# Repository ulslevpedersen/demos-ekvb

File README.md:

# demos-ekvb
DEMoS Manifesto
https://arxiv.org/licenses/nonexclusive-distrib/1.0/license.html

This project contains also the tpIP implementation in F#

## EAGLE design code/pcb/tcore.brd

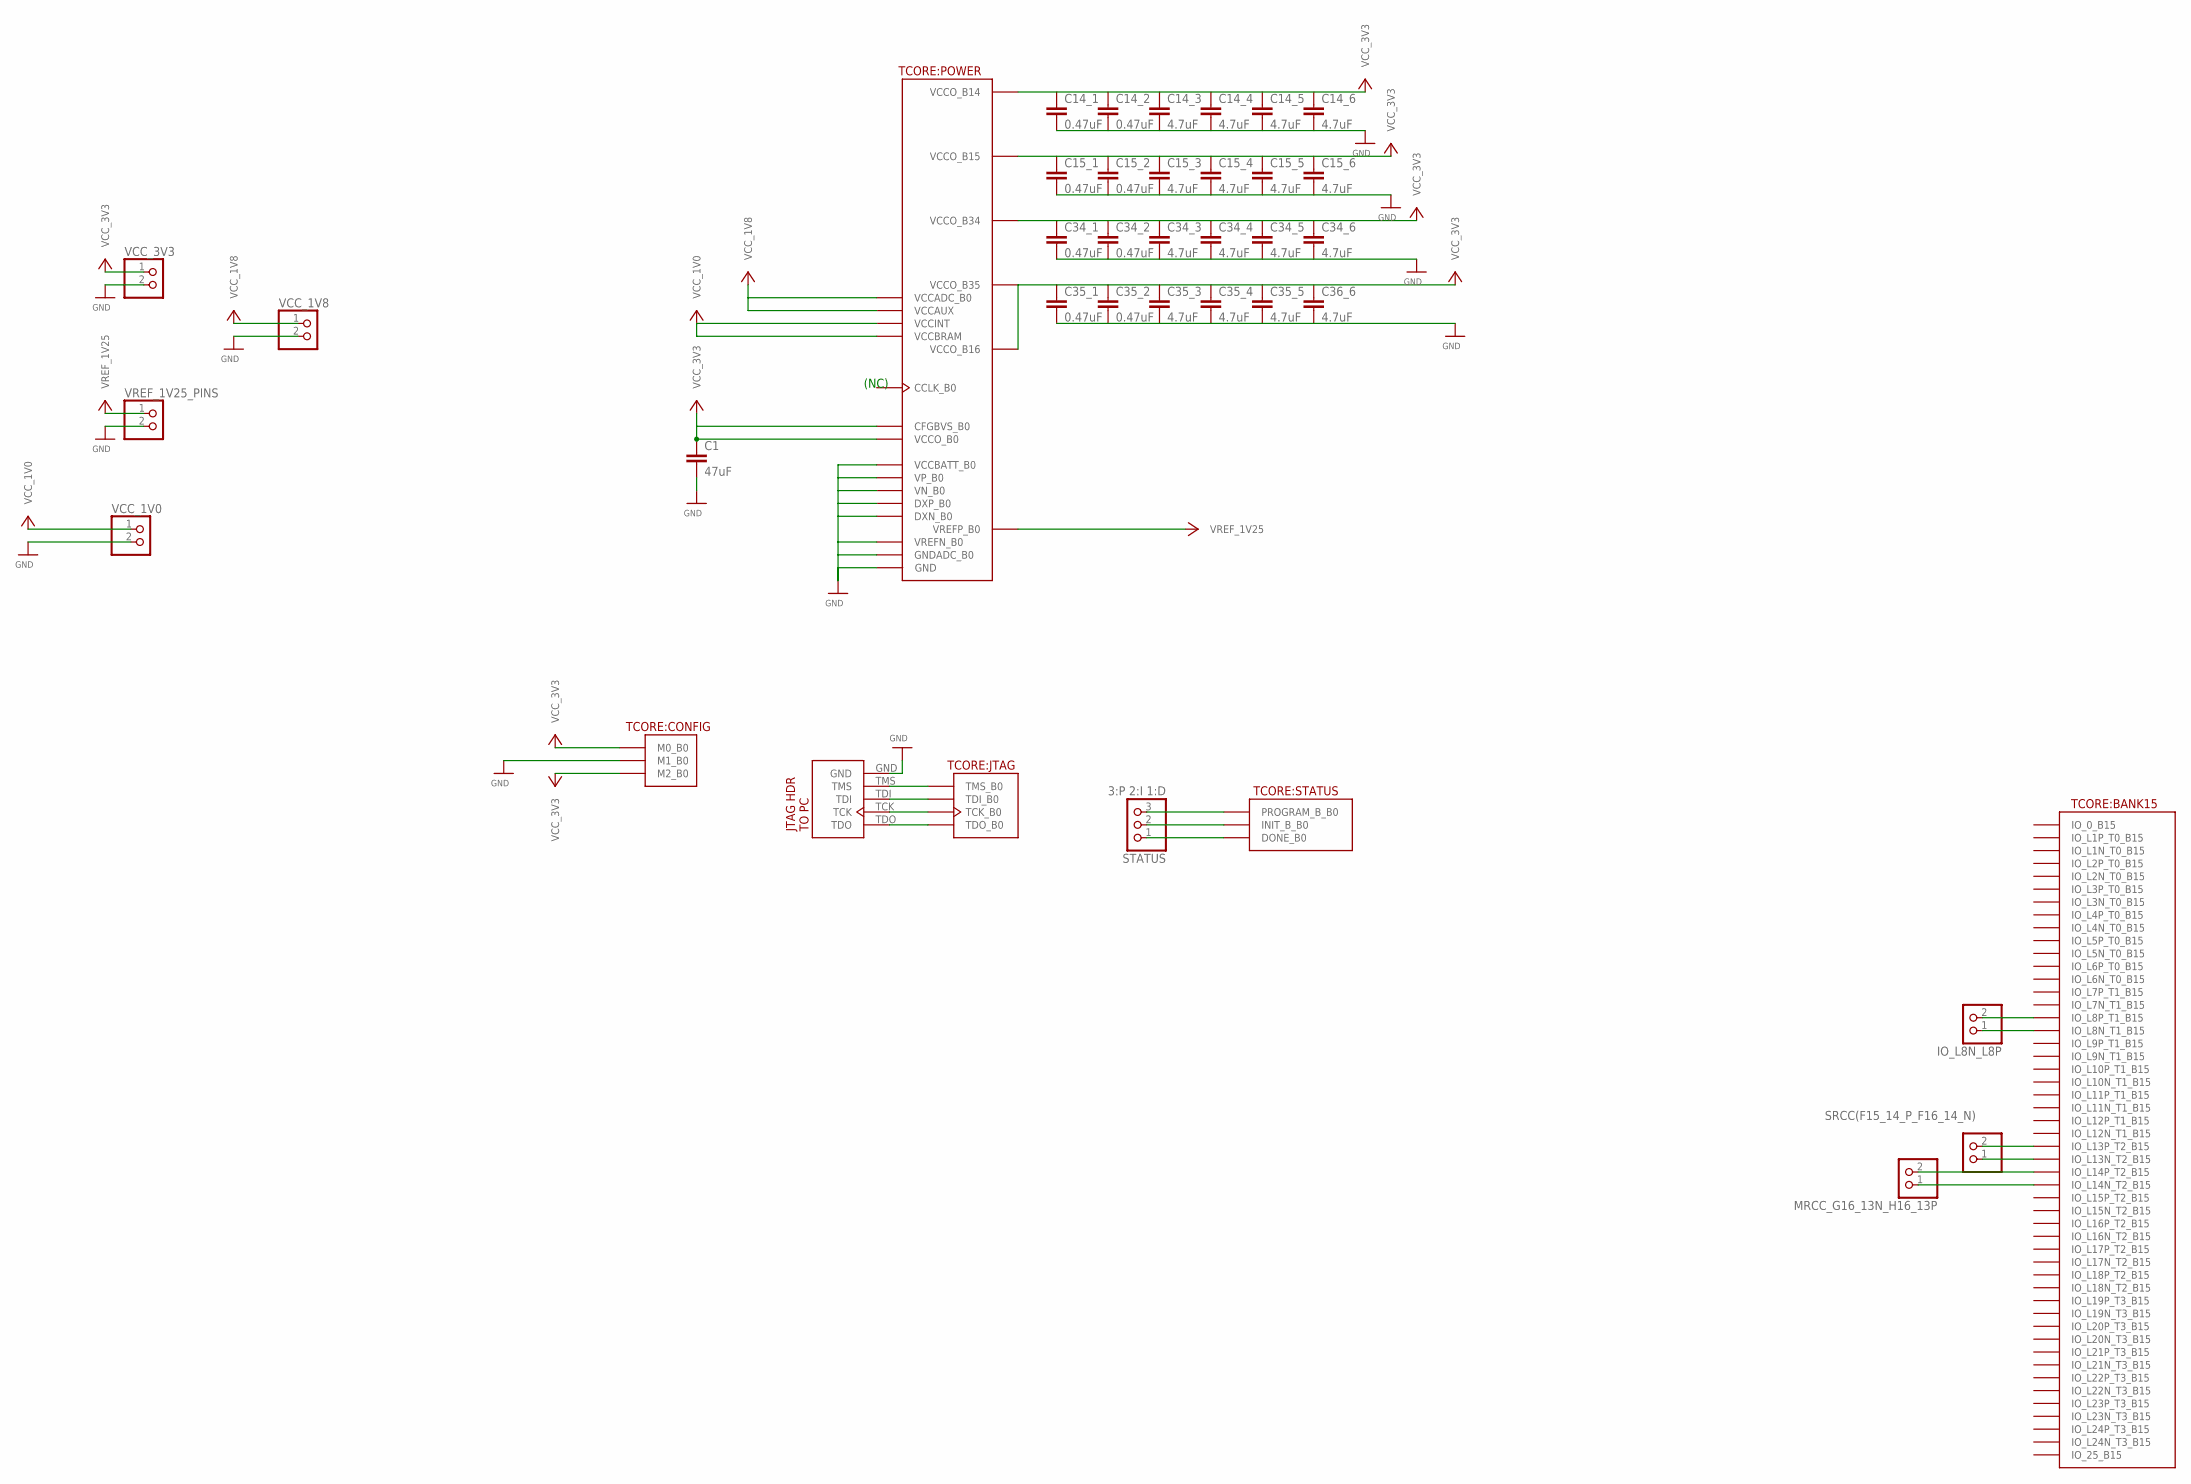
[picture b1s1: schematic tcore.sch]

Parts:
C1: 47uF; C1206
C14_1, C14_2, C15_1, C15_2, C34_1, C34_2, C35_1, C35_2: 0.47uF; C1206
C14_3, C14_4, C14_5, C14_6, C15_3, C15_4, C15_5, C15_6, C34_3, C34_4, C34_5, C34_6, C35_3, C35_4, C35_5, C36_6: 4.7uF; C1206
IO_L8N_L8P: PINHD-1X2; 1X02
JTAG_HEADER1: JTAG_HEADER; JTAG_HDR
MRCC_G16_13N_H16_13P: PINHD-1X2; 1X02
SRCC(F15_14_P_F16_14_N): PINHD-1X2; 1X02
STATUS: 3:P 2:I 1:D; 1X03
TCORE: TCORECFG324; TCORE_PAC
VCC_1V0, VCC_1V8, VCC_3V3: PINHD-1X2; 1X02
VREF_1V25_PINS: PINHD-1X2; 1X02

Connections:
GND: C1.2, C14_1.2, C15_1.2, C34_1.2, C35_1.2, JTAG_HEADER1.GND, TCORE.A02@GND (GND), TCORE.A12@GND (GND), TCORE.B05@GND (GND), TCORE.B15@GND (GND), TCORE.C08@GND (GND), TCORE.C18@GND (GND), TCORE.D01@GND (GND), TCORE.D11@GND (GND), TCORE.E04@GND (GND), TCORE.E08@VCCBATT_B0 (VCCBATT_B0), TCORE.E14@GND (GND), TCORE.F07@GND (GND), TCORE.F09@GND (GND), TCORE.F11@GND (GND), TCORE.F17@GND (GND), TCORE.G08@GND (GND), TCORE.G10@GND (GND), TCORE.G12@GND (GND), TCORE.H03@GND (GND), TCORE.H07@GND (GND), TCORE.H09@GNDADC_B0 (GNDADC_B0), TCORE.H11@GND (GND), TCORE.H13@GND (GND), TCORE.J06@GND (GND), TCORE.J08@GND (GND), TCORE.J09@VREFN_0 (VREFN_B0), TCORE.J10@VP_0 (VP_B0), TCORE.J12@GND (GND), TCORE.J16@GND (GND), TCORE.K07@GND (GND), TCORE.K09@VN_B0 (VN_B0), TCORE.K11@GND (GND), TCORE.L02@GND (GND), TCORE.L08@GND (GND), TCORE.L09@DXN_B0 (DXN_B0), TCORE.L10@DXP_B0 (DXP_B0), TCORE.L12@GND (GND), TCORE.M05@GND (GND), TCORE.M07@GND (GND), TCORE.M09@GND (GND), TCORE.M11@GND (GND), TCORE.M15@GND (GND), TCORE.N08@GND (GND), TCORE.N10@GND (GND), TCORE.N12@GND (GND), TCORE.N18@GND (GND), TCORE.P01@GND (GND), TCORE.P13@M1_B0 (M1_B0), TCORE.R04@GND (GND), TCORE.R14@GND (GND), TCORE.T07@GND (GND), TCORE.T17@GND (GND), TCORE.U10@GND (GND), TCORE.V03@GND (GND), TCORE.V13@GND (GND), VCC_1V0.2, VCC_1V8.2, VCC_3V3.2, VREF_1V25_PINS.2
unnamed: JTAG_HEADER1.TDO, TCORE.E13@TDO_B0 (TDO_B0)
unnamed: JTAG_HEADER1.TCK, TCORE.E10@TCK_B0 (TCK_B0)
unnamed: JTAG_HEADER1.TDI, TCORE.E11@TDI_B0 (TDI_B0)
unnamed: JTAG_HEADER1.TMS, TCORE.E12@TMS_B0 (TMS_B0)
unnamed: STATUS.3, TCORE.P09@PROGRAM_B_B0 (PROGRAM_B_B0)
unnamed: STATUS.2, TCORE.P07@INIT_B_B0 (INIT_B_B0)
unnamed: STATUS.1, TCORE.P10@DONE_B0 (DONE_B0)
unnamed: IO_L8N_L8P.2, TCORE.A15@IO_L8P_T1_B15 (IO_L8P_T1_B15)
unnamed: MRCC_G16_13N_H16_13P.1, TCORE.F16@IO_L14N_T2_B15 (IO_L14N_T2_B15)
unnamed: MRCC_G16_13N_H16_13P.2, TCORE.F15@IO_L14P_T2_B15 (IO_L14P_T2_B15)
unnamed: SRCC(F15_14_P_F16_14_N).1, TCORE.G16@IO_L13N_T2_B15 (IO_L13N_T2_B15)
unnamed: SRCC(F15_14_P_F16_14_N).2, TCORE.H16@IO_L13P_T2_B15 (IO_L13P_T2_B15)
unnamed: IO_L8N_L8P.1, TCORE.A16@IO_L8N_T1_B15 (IO_L8N_T1_B15)
VCCO_B14: C1.1, TCORE.A07@VCCO_B35 (VCCO_B35), TCORE.B10@VCCO_B16 (VCCO_B16), TCORE.C03@VCCO_B35 (VCCO_B35), TCORE.D06@VCCO_B35 (VCCO_B35), TCORE.F02@VCCO_B35 (VCCO_B35), TCORE.G05@VCCO_B35 (VCCO_B35), TCORE.J01@VCCO_B35 (VCCO_B35), TCORE.K04@VCCO_B34 (VCCO_B34), TCORE.L17@VCCO_B14 (VCCO_B14), TCORE.N03@VCCO_B34 (VCCO_B34), TCORE.N13@VCCO_14 (VCCO_B14), TCORE.P06@VCCO_B34 (VCCO_B34), TCORE.P08@CFGBVS_0B (CFGBVS_B0), TCORE.P16@VCCO_14 (VCCO_B14), TCORE.R09@VCCO_B0 (VCCO_B0), TCORE.T02@VCCO_B34 (VCCO_B34), TCORE.T12@VCCO_B14 (VCCO_B14), TCORE.U05@VCCO_B34 (VCCO_B34), TCORE.U15@VCCO_B14 (VCCO_B14), TCORE.V08@VCCO_B34 (VCCO_B34), TCORE.V18@VCCO_B14 (VCCO_B14), VCC_3V3.1
VCCO_B15: TCORE.A17@VCCO_B15 (VCCO_B15), TCORE.C13@VCCO_B15 (VCCO_B15), TCORE.D16@VCCO_B15 (VCCO_B15), TCORE.G15@VCCO_15 (VCCO_B15), TCORE.H18@VCCO_B15 (VCCO_B15), TCORE.K14@VCCO_B15 (VCCO_B15)
VCC_1V0: TCORE.F08@VCCINT (VCCINT), TCORE.F10@VCCBRAM (VCCBRAM), TCORE.G07@VCCINT (VCCINT), TCORE.G09@VCCINT (VCCINT), TCORE.G11@VCCBRAM (VCCBRAM), TCORE.H08@VCCINT (VCCINT), TCORE.J07@VCCINT (VCCINT), TCORE.J11@VCCINT (VCCINT), TCORE.K08@VCCINT (VCCINT), TCORE.L07@VCCINT (VCCINT), TCORE.L11@VCCINT (VCCINT), TCORE.M08@VCCINT (VCCINT), TCORE.M10@VCCINT (VCCINT), TCORE.N07@VCCINT (VCCINT), TCORE.N09@VCCINT (VCCINT), TCORE.N11@VCCINT (VCCINT), VCC_1V0.1
VCC_1V8: TCORE.F12@VCCAUX (VCCAUX), TCORE.H10@VCCADC_B0 (VCCADC_B0), TCORE.H12@VCCAUX (VCCAUX), TCORE.K12@VCCAUX (VCCAUX), TCORE.M12@VCCAUX (VCCAUX), VCC_1V8.1
VCC_3V3: TCORE.P11@M2_B0 (M2_B0), TCORE.P12@M0_B0 (M0_B0)
VREF_1V25: TCORE.K10@VREFP_B0 (VREFP_B0), VREF_1V25_PINS.1

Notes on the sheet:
(NC)

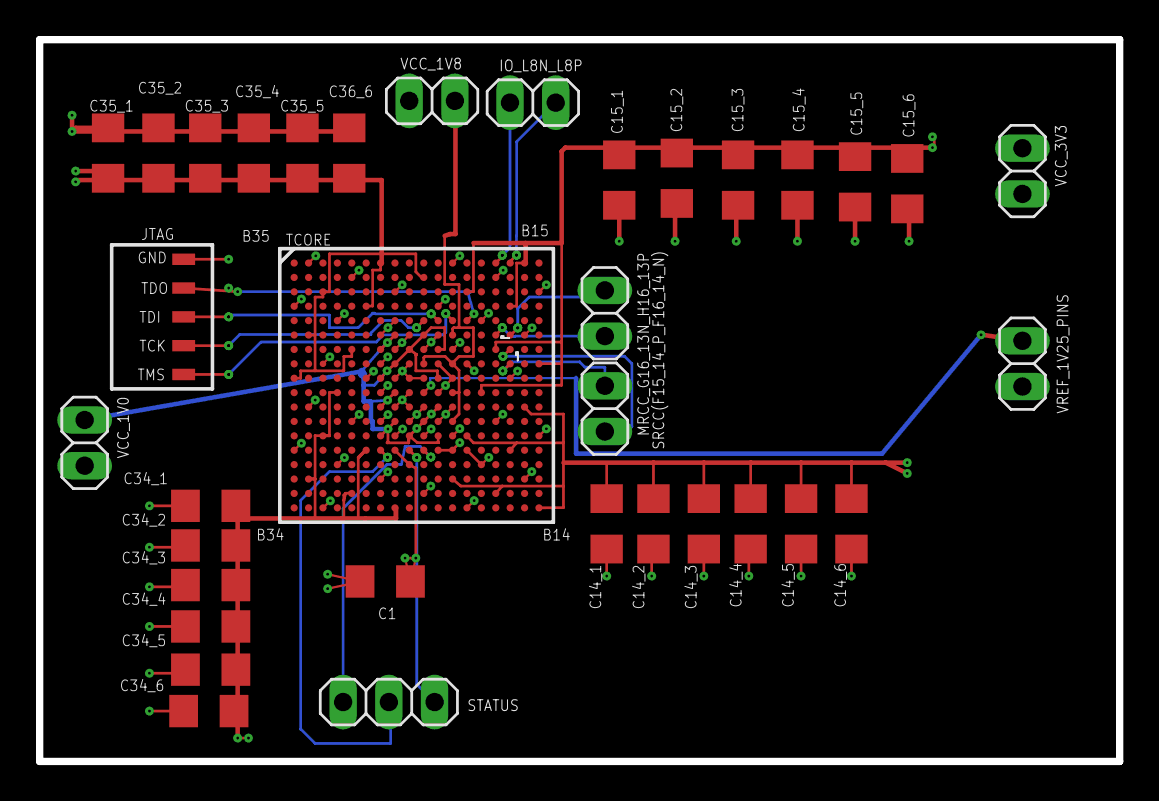
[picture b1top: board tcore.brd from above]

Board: 4 copper layers, 60.0 x 40.1 mm, 35 parts (0 on the bottom side), 20 nets.

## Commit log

2017-03-07 demos-ekvb: mish code files
2017-03-10 demos: makefile like the tcl scripts
2017-03-20 demos: updated to give a little help and added a clean target
2017-03-21 demos: renamed hw->pcb
2017-03-21 demos: updated hw Makefile
2017-09-24 LIPS: Little IP Stack init
2017-09-26 lips: IP checksum correction
2017-09-28 lips: Option type for URL
2017-09-30 lips: testing text/plain vs text/html
2017-09-30 lips: better output and shared http lib
2017-10-01 lips: one http module
2017-10-02 lips: queue
2017-10-04 tpip: tx queue
2017-10-12 lips/tpip: change HTTP "Connection" header to "close"
2017-10-17 lips: starting udp
2017-10-18 lips: ip in udp
2017-10-21 lips/tpip: upd print util and async udp loop
2017-10-23 lips/tpip: UDP server datagram detection
2017-10-24 fop: main loop formatting
2017-10-29 lips: disabled queue lock
2017-11-01 demop/fop: changed = to <=
2017-11-05 fop: loading in task instead of initial begin
2017-11-06 fop: load and unit delays for sim
2017-11-07 fop: boot sequence
2017-11-08 fop: cilSwitch challenge w. default
2017-11-09 lips: todo/redo the interface to the queue (periodic poll and no lock)
2017-11-11 demos: gmi
